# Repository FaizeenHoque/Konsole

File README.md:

# KONSOLE
Konsole built by FaixeN for Hack Club’s Blueprint Program. It features a mini console design with 8 push buttons, an oled screen and a on off switch.

## CAD Model

## PCB

This is the PCB for the small handheld console. It includes the buttons, display, Pico, and other parts all routed together on a compact board. The layout is designed to be easy to hold, simple to build, and portable enough to take anywhere. All traces are cleaned up and organized so the console works reliably and stays easy to update in the future.

## Assembled

## Firmware

## BOM (Bill of Materials)

## Credits
Made by: [@faizeenhoque](https://github.com/FaizeenHoque)

## License
[MIT](https://choosealicense.com/licenses/mit/)

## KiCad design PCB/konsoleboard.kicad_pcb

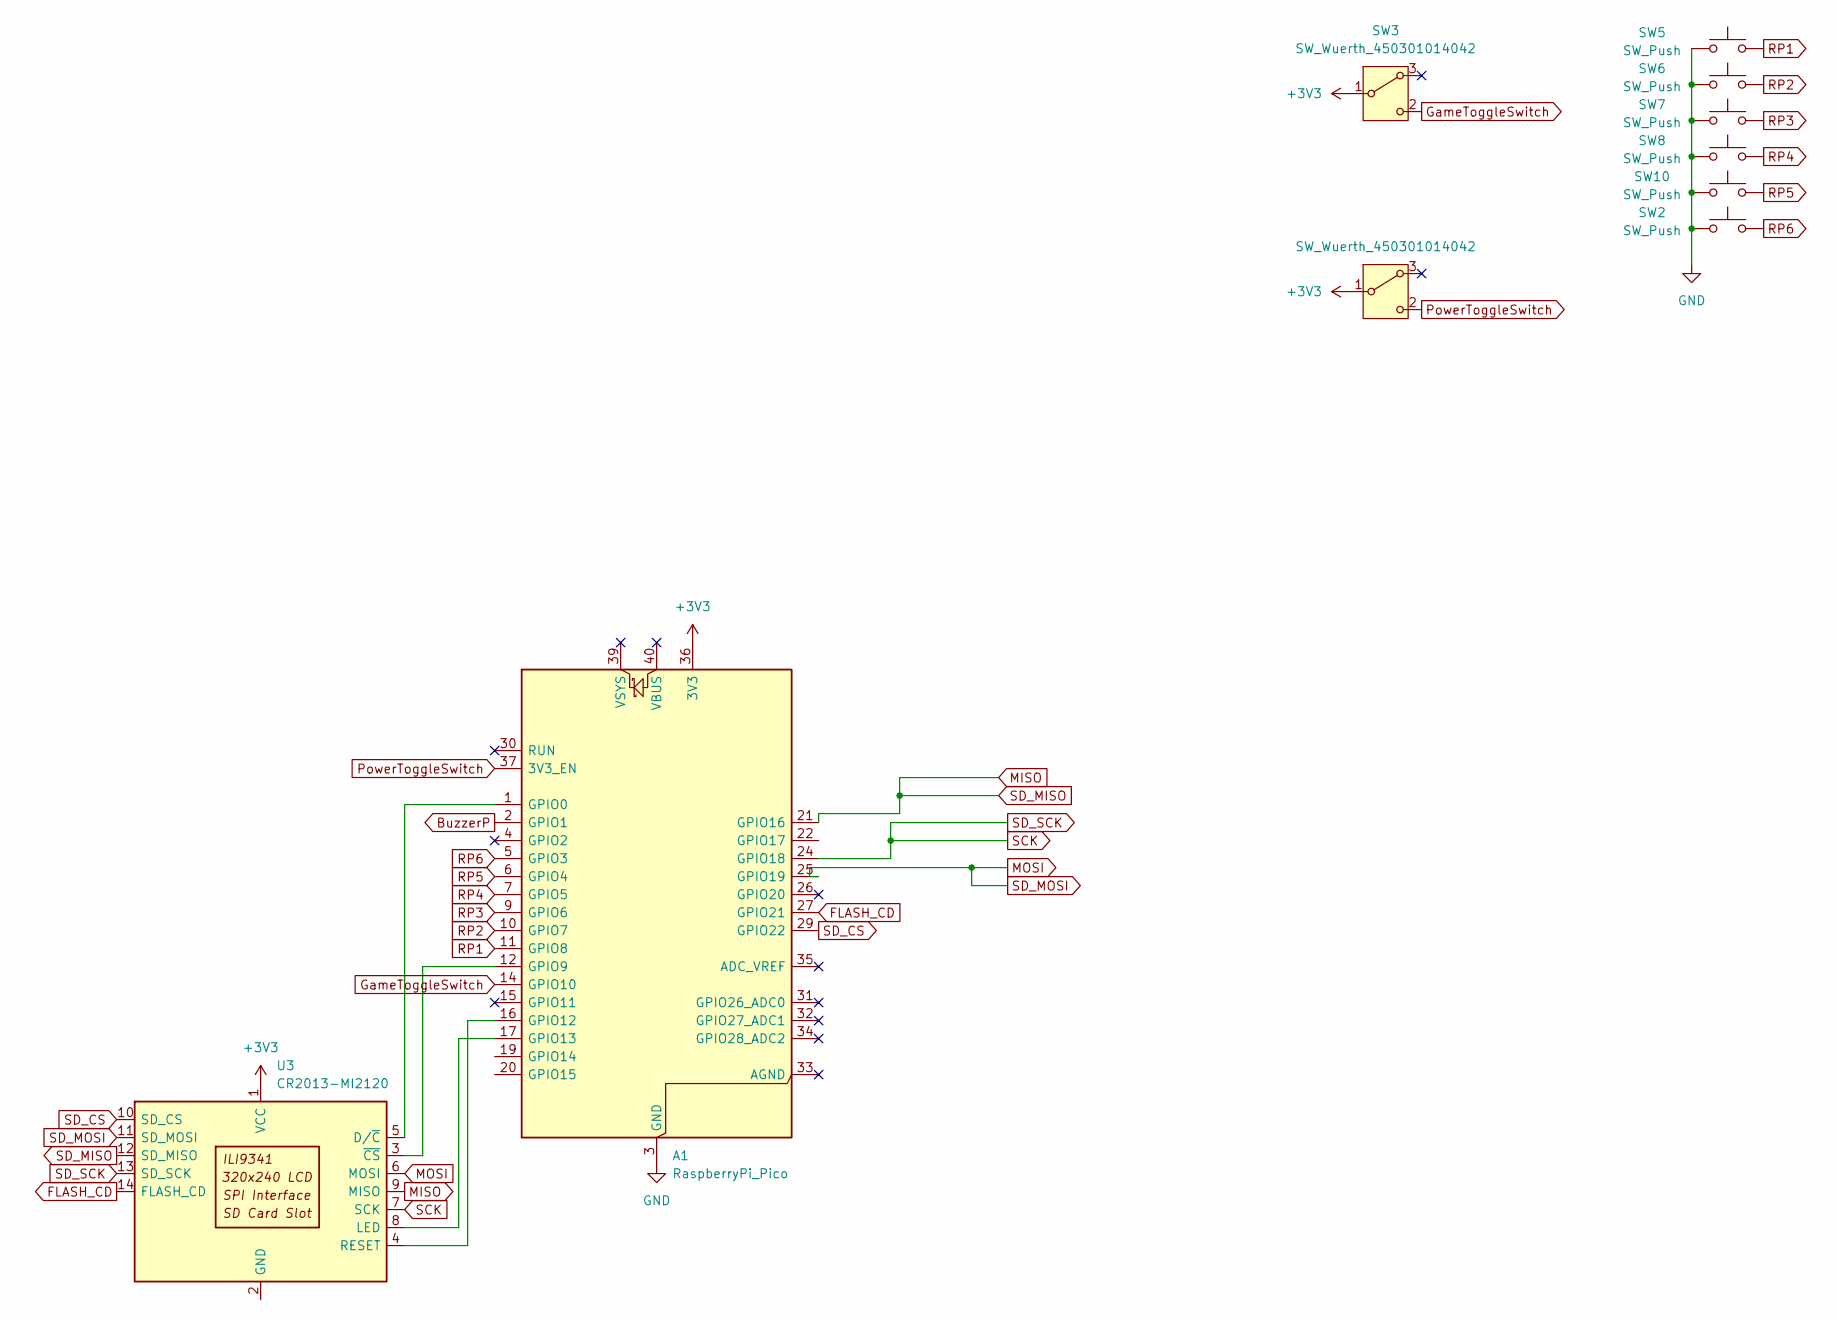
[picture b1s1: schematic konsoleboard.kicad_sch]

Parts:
A1: RaspberryPi_Pico; RaspberryPi_Pico_Common_THT
SW2, SW5, SW6, SW7, SW8, SW10: SW_Push; SW_PUSH-12mm
SW3, SW9: SW_Wuerth_450301014042; SW_Slide-03_Wuerth-WS-SLTV_10x2.5x6.4_P2.54mm
U3: CR2013-MI2120

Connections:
+3V3: A1.36 (3V3), SW3.1 (B), SW9.1 (B), U3.1 (VCC)
BuzzerP: A1.2 (GPIO1)
FLASH_CD: A1.27 (GPIO21), U3.14 (FLASH_CD)
GND: A1.3 (GND), A1.8 (GND), A1.13 (GND), A1.18 (GND), A1.23 (GND), A1.28 (GND), A1.38 (GND), SW2.1, SW5.1, SW6.1, SW7.1, SW8.1, SW10.1
GameToggleSwitch: A1.14 (GPIO10), SW3.2 (C)
MISO: A1.21 (GPIO16), U3.9 (MISO), U3.12 (SD_MISO)
MOSI: A1.25 (GPIO19), U3.6 (MOSI), U3.11 (SD_MOSI)
unnamed: A1.1 (GPIO0), U3.5 (D/~C)
unnamed: A1.12 (GPIO9), U3.3 (~CS)
unnamed: A1.16 (GPIO12), U3.4 (RESET)
unnamed: A1.17 (GPIO13), U3.8 (LED)
PowerToggleSwitch: A1.37 (3V3_EN), SW9.2 (C)
RP1: A1.11 (GPIO8), SW5.2
RP2: A1.10 (GPIO7), SW6.2
RP3: A1.9 (GPIO6), SW7.2
RP4: A1.7 (GPIO5), SW8.2
RP5: A1.6 (GPIO4), SW10.2
RP6: A1.5 (GPIO3), SW2.2
SCK: A1.24 (GPIO18), U3.7 (SCK), U3.13 (SD_SCK)
SD_CS: A1.29 (GPIO22), U3.10 (SD_CS)

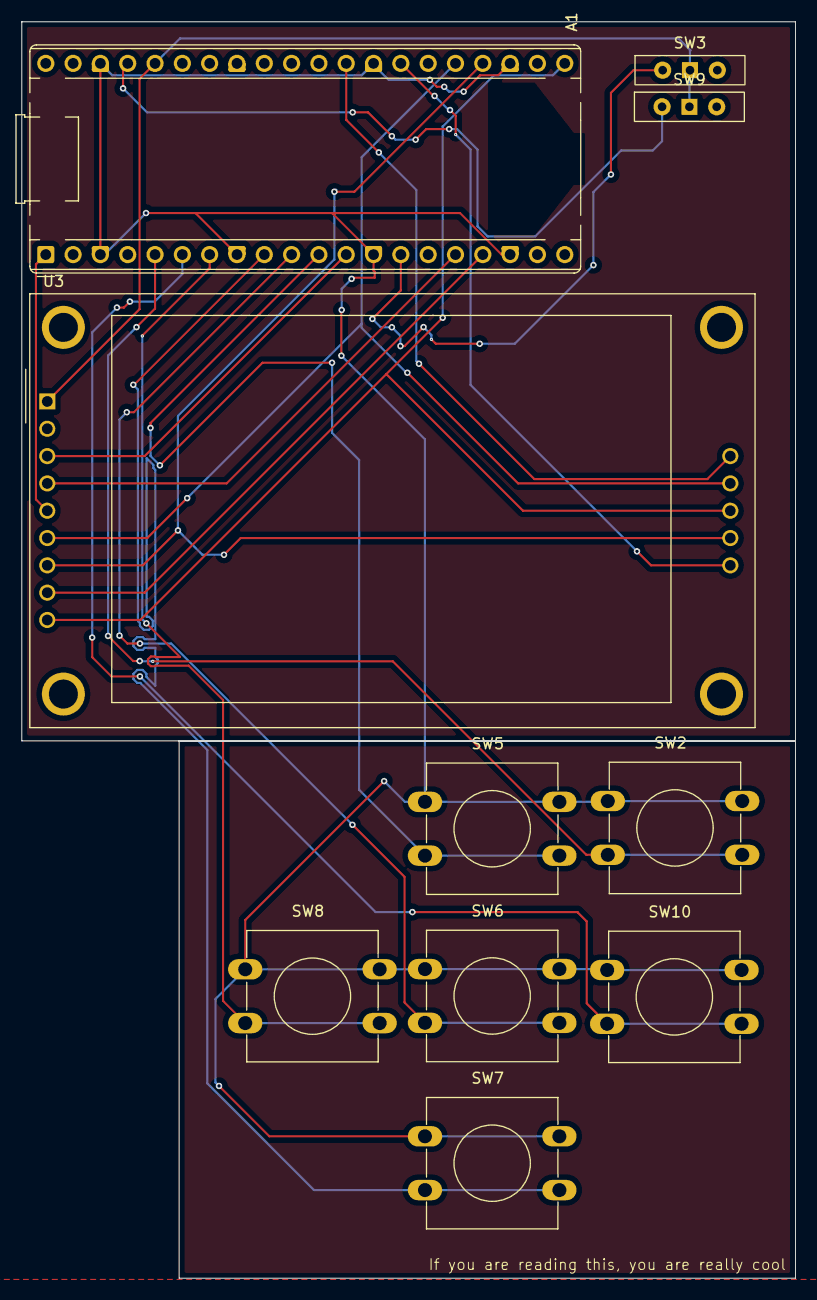
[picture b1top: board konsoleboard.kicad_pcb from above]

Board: 2 copper layers, 71.9 x 116.8 mm, 10 parts (0 on the bottom side), 19 nets.

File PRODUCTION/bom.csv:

Designator,Footprint,Quantity,Value,LCSC Part #
A1,RaspberryPi_Pico_Common_THT,1,RaspberryPi_Pico,
"SW10, SW2, SW5, SW6, SW7, SW8",SW_PUSH-12mm,6,SW_Push,
"SW3, SW9",SW_Slide-03_Wuerth-WS-SLTV_10x2.5x6.4_P2.54mm,2,SW_Wuerth_450301014042,
U3,CR2013-MI2120,1,CR2013-MI2120,

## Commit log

2025-12-05 Added a base README file
2025-12-05 Added a FIRMWARE folder, Initialized KiCad project in PCB directory
2025-12-06 Finished making the schematic, imma work on the PCB next
2025-12-07 Added 2 more slide switch things for game pause and buzzer toggle, added a bigger display and repositioned most of the components
2025-12-08 Completed the pcb routing
2025-12-08 Added Branding and Filled Zone
2025-12-08 Generated JLCPCB Fabrication files
2025-12-08 Enhance README with PCB details and images
    Added detailed description of the PCB layout and included images for better visualization.
2025-12-08 Decided to remove the buzzer and the buzzer switch
